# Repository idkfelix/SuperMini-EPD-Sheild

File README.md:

## Referances
<https://www.pervasivedisplays.com/wp-content/uploads/2021/12/1P266-00_03_E2213CS0C2_20211203.pdf>
<https://www.hirose.com/en/product/document?clcode=CL0580-1255-6-50&productname=FH34SRJ-24S-0.5SH(50)&series=FH34SRJ&documenttype=2DDrawing&lang=en&documentid=0001483059>
<https://www.tindie.com/products/adz1122/esp32-c3-development-board-esp32-supermini/>

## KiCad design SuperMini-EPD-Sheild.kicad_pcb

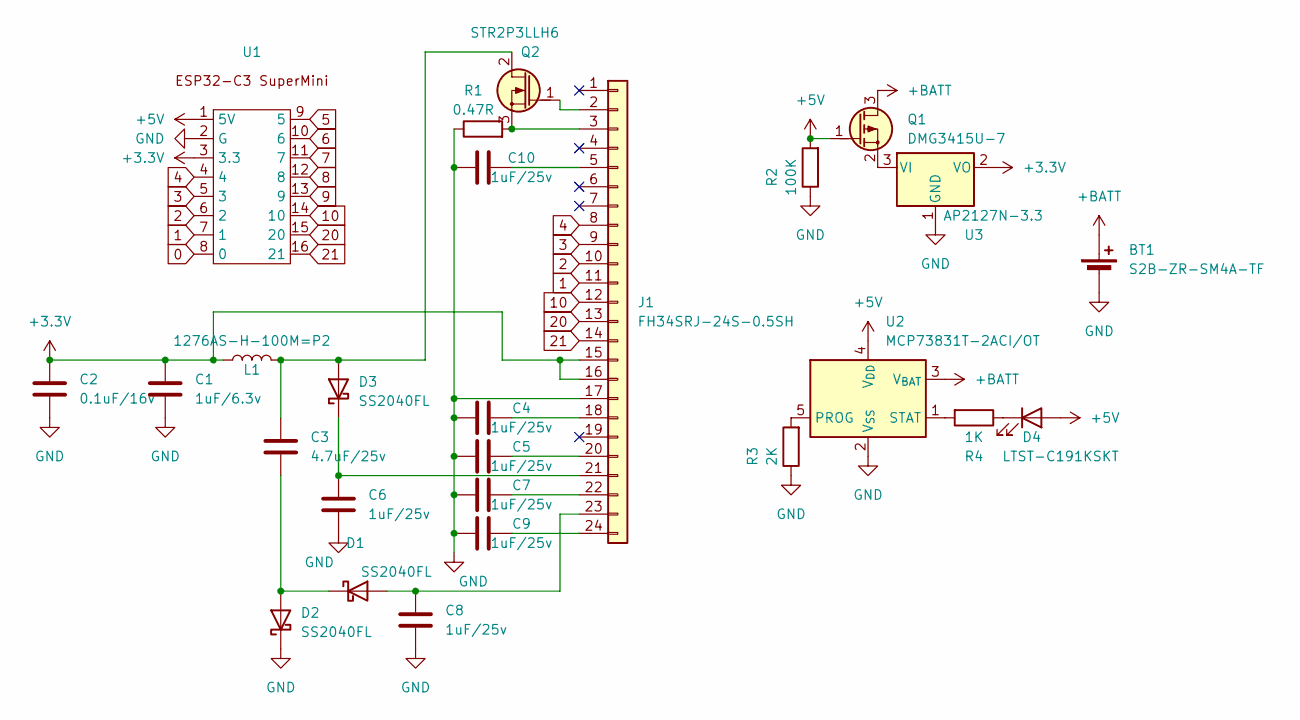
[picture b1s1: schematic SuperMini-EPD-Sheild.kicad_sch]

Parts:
BT1: S2B-ZR-SM4A-TF; JST_PH_S2B-PH-SM4-TB_1x02-1MP_P2.00mm_Horizontal
C1: 1uF/6.3v; C_0603_1608Metric
C2: 0.1uF/16v; C_0603_1608Metric
C3: 4.7uF/25v; C_0603_1608Metric
C4, C5, C6, C7, C8, C9, C10: 1uF/25v; C_0603_1608Metric
D1, D2, D3: SS2040FL; D_0603_1608Metric
D4: LTST-C191KSKT; LED_0603_1608Metric
J1: FH34SRJ-24S-0.5SH
L1: 1276AS-H-100M=P2; L_1210_3225Metric
Q1: DMG3415U-7; SC-59
Q2: STR2P3LLH6; SC-59
R1: 0.47R; R_0603_1608Metric
R2: 100K; R_0603_1608Metric
R3: 2K; R_0603_1608Metric
R4: 1K; R_0603_1608Metric
U1: esp32-c3 superMini
U2: MCP73831T-2ACI/OT; SOT-23-5
U3: AP2127N-3.3; SOT-23

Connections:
0: U1.8 (0)
1: J1.11, U1.7 (1)
2: J1.10, U1.6 (2)
3: J1.9, U1.5 (3)
4: J1.8, U1.4
5: U1.9 (5)
6: U1.10 (6)
7: U1.11 (7)
8: U1.12 (8)
9: U1.13 (9)
10: J1.12, U1.14 (10)
20: J1.13, U1.15 (20)
21: J1.14, U1.16 (21)
+3.3V: C1.1, C2.1, J1.15, J1.16, L1.1, U1.3 (3.3), U3.2 (VO)
+5V: D4.2 (A), Q1.1 (G), R2.2, U1.1 (5V), U2.4 (V_{DD})
+BATT: BT1.1 (+), Q1.3 (D), U2.3 (V_{BAT})
GND: BT1.2 (-), C1.2, C2.2, C4.1, C5.1, C6.2, C7.1, C8.2, C9.1, C10.1, D2.1 (K), J1.17, R1.1, R2.1, R3.1, U1.2 (G), U2.2 (V_{SS}), U3.1 (GND)
unnamed: C8.1, D1.2 (A), J1.23
unnamed: C3.2, D1.1 (K), D2.2 (A)
unnamed: C3.1, D3.2 (A), L1.2, Q2.2 (D)
unnamed: C6.1, D3.1 (K), J1.21
unnamed: D4.1 (K), R4.1
unnamed: J1.2, Q2.1 (G)
unnamed: J1.3, Q2.3 (S), R1.2
unnamed: C10.2, J1.5
unnamed: C4.2, J1.18
unnamed: C5.2, J1.20
unnamed: C7.2, J1.22
unnamed: C9.2, J1.24
unnamed: Q1.2 (S), U3.3 (VI)
unnamed: R3.2, U2.5 (PROG)
unnamed: R4.2, U2.1 (STAT)

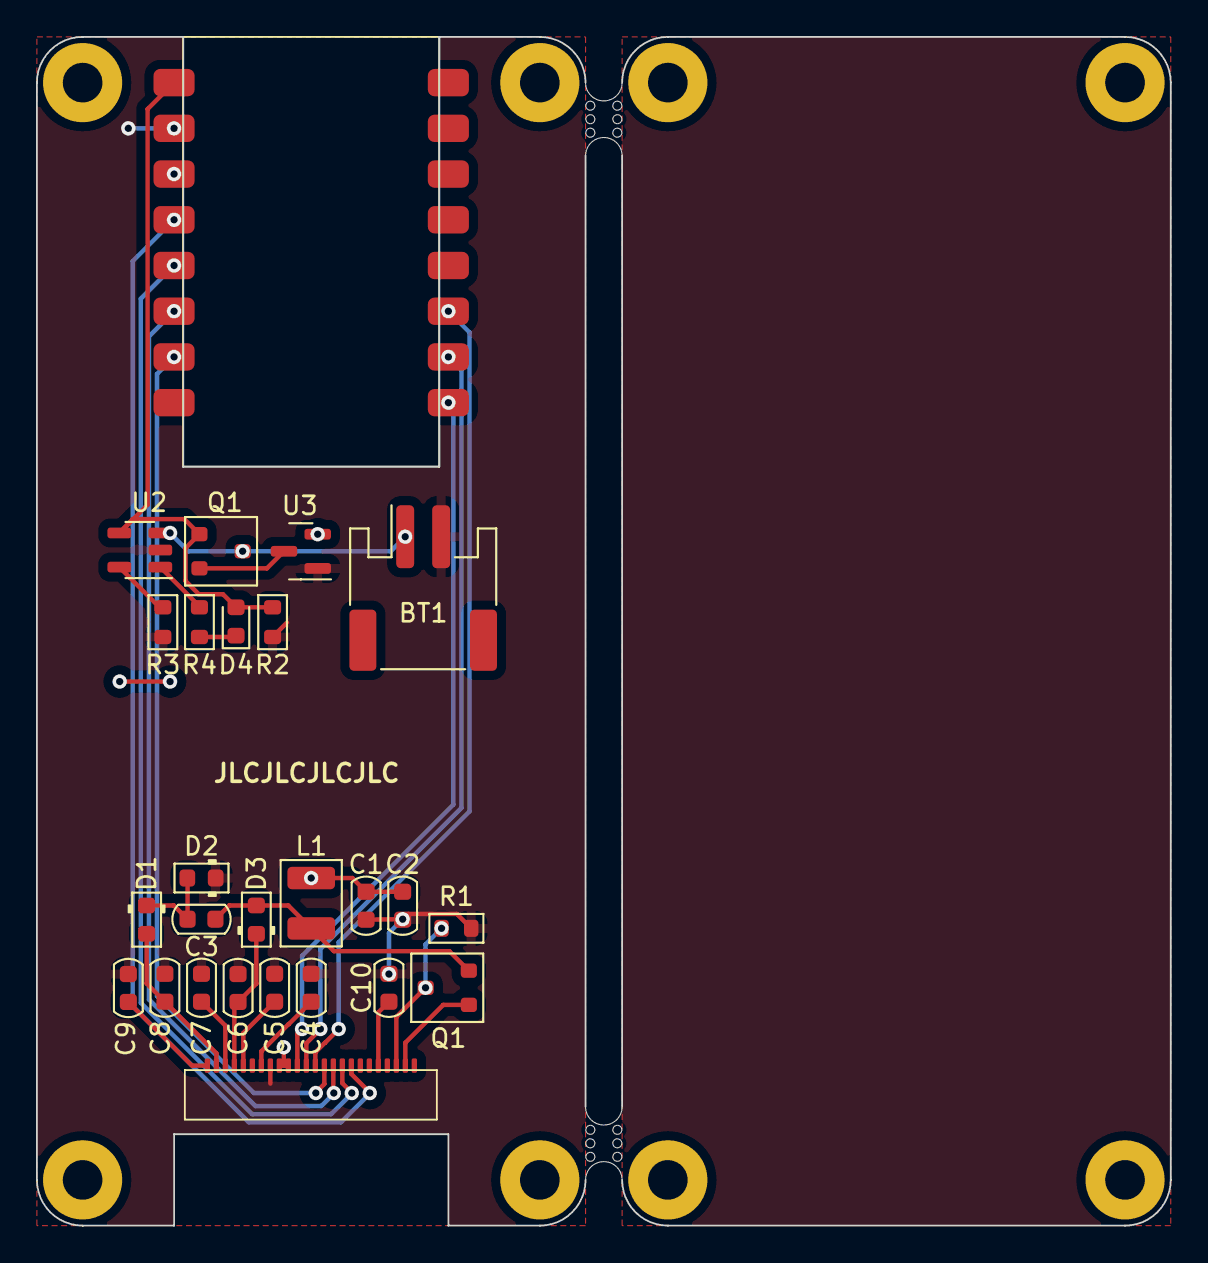
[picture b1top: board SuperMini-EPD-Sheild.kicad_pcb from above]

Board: 2 copper layers, 63.0 x 66.0 mm, 28 parts (0 on the bottom side), 26 nets.

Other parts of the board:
mouse-bite-2mm-slot, mouse-bite-2mm-slot#2: VAL**; mouse-bite-2mm-slot
